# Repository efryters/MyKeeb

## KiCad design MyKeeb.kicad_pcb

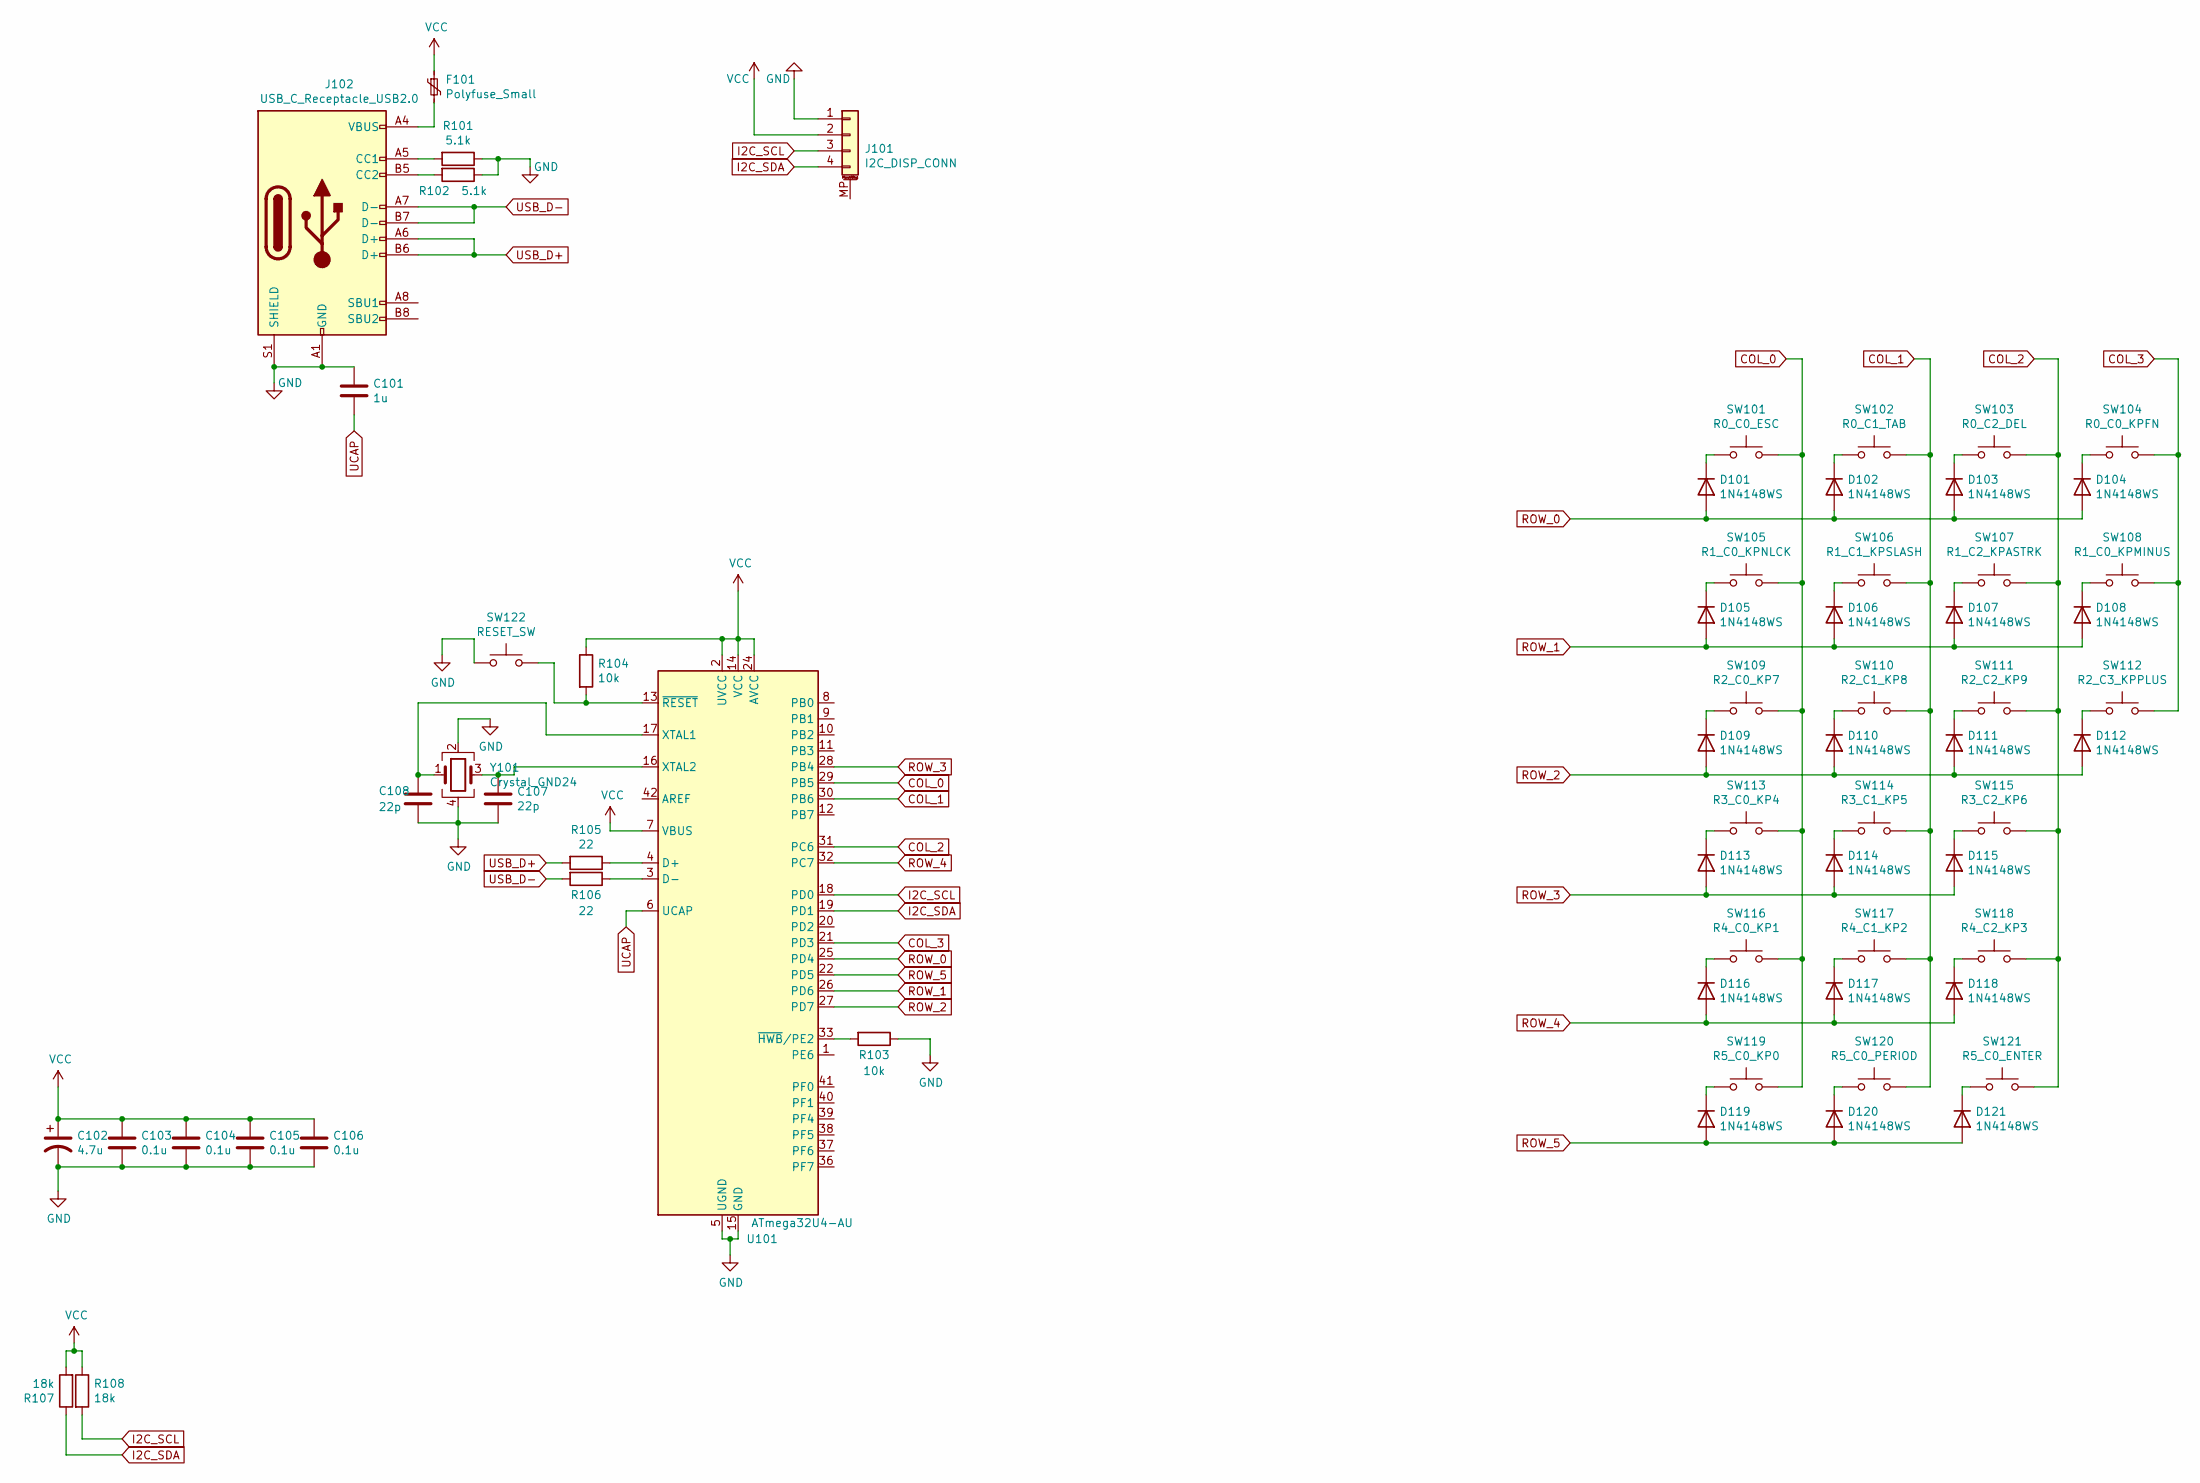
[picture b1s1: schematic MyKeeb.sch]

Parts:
C101: 1u; C_0603_1608Metric_Pad1.08x0.95mm_HandSolder
C102: 4.7u; C_Elec_4x5.4
C103, C104, C105, C106: 0.1u; C_0603_1608Metric_Pad1.08x0.95mm_HandSolder
C107, C108: 22p; C_0603_1608Metric_Pad1.08x0.95mm_HandSolder
D101, D102, D103, D104, D105, D106, D107, D108, D109, D110, D111, D112, D113, D114, D115, D116, D117, D118, D119, D120, D121: 1N4148WS; D_SOD-323
F101: Polyfuse_Small; Fuse_1206_3216Metric_Pad1.42x1.75mm_HandSolder
J101: I2C_DISP_CONN; PinSocket_1x04_P2.54mm_Horizontal
J102: USB_C_Receptacle_USB2.0; USB_C_Receptacle_GCT_USB4085
R101, R102: 5.1k; R_0603_1608Metric
R103, R104: 10k; R_0603_1608Metric
R105, R106: 22; R_0603_1608Metric
R107, R108: 18k; R_0603_1608Metric
SW101: R0_C0_ESC; SW_Cherry_MX_PCB_1.00u
SW102: R0_C1_TAB; SW_Cherry_MX_PCB_1.00u
SW103: R0_C2_DEL; SW_Cherry_MX_PCB_1.00u
SW104: R0_C0_KPFN; SW_Cherry_MX_PCB_1.00u
SW105: R1_C0_KPNLCK; SW_Cherry_MX_PCB_1.00u
SW106: R1_C1_KPSLASH; SW_Cherry_MX_PCB_1.00u
SW107: R1_C2_KPASTRK; SW_Cherry_MX_PCB_1.00u
SW108: R1_C0_KPMINUS; SW_Cherry_MX_PCB_1.00u
SW109: R2_C0_KP7; SW_Cherry_MX_PCB_1.00u
SW110: R2_C1_KP8; SW_Cherry_MX_PCB_1.00u
SW111: R2_C2_KP9; SW_Cherry_MX_PCB_1.00u
SW112: R2_C3_KPPLUS; SW_Cherry_MX_PCB_2.00u_Rotated
SW113: R3_C0_KP4; SW_Cherry_MX_PCB_1.00u
SW114: R3_C1_KP5; SW_Cherry_MX_PCB_1.00u
SW115: R3_C2_KP6; SW_Cherry_MX_PCB_1.00u
SW116: R4_C0_KP1; SW_Cherry_MX_PCB_1.00u
SW117: R4_C1_KP2; SW_Cherry_MX_PCB_1.00u
SW118: R4_C2_KP3; SW_Cherry_MX_PCB_1.00u
SW119: R5_C0_KP0; SW_Cherry_MX_PCB_2.00u
SW120: R5_C0_PERIOD; SW_Cherry_MX_PCB_1.00u
SW121: R5_C0_ENTER; SW_Cherry_MX_PCB_2.00u_Rotated
SW122: RESET_SW; SW_SPST_SKQG_WithoutStem
U101: ATmega32U4-AU; TQFP-44_10x10mm_P0.8mm
Y101: Crystal_GND24; Crystal_SMD_Abracon_ABM3B-4Pin_5.0x3.2mm

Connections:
COL_0: SW101.2, SW105.2, SW109.2, SW113.2, SW116.2, SW119.2, U101.29 (PB5)
COL_1: SW102.2, SW106.2, SW110.2, SW114.2, SW117.2, SW120.2, U101.30 (PB6)
COL_2: SW103.2, SW107.2, SW111.2, SW115.2, SW118.2, SW121.2, U101.31 (PC6)
COL_3: SW104.2, SW108.2, SW112.2, U101.21 (PD3)
GND: C101.1, C102.2, C103.2, C104.2, C105.2, C106.2, C107.2, C108.2, J101.1, J102.A1 (GND), J102.A12 (GND), J102.B1 (GND), J102.B12 (GND), J102.S1 (SHIELD), R101.1, R102.1, R103.1, SW122.1, U101.5 (UGND), U101.15 (GND), U101.23 (GND), U101.35 (GND), U101.43 (GND), Y101.2, Y101.4
I2C_SCL: J101.3, R108.2, U101.18 (PD0)
I2C_SDA: J101.4, R107.1, U101.19 (PD1)
unnamed: C107.1, U101.16 (XTAL2), Y101.3
unnamed: C108.1, U101.17 (XTAL1), Y101.1
unnamed: D101.1 (K), SW101.1
unnamed: D102.1 (K), SW102.1
unnamed: D103.1 (K), SW103.1
unnamed: D104.1 (K), SW104.1
unnamed: D105.1 (K), SW105.1
unnamed: D106.1 (K), SW106.1
unnamed: D107.1 (K), SW107.1
unnamed: D108.1 (K), SW108.1
unnamed: D109.1 (K), SW109.1
unnamed: D110.1 (K), SW110.1
unnamed: D111.1 (K), SW111.1
unnamed: D112.1 (K), SW112.1
unnamed: D113.1 (K), SW113.1
unnamed: D114.1 (K), SW114.1
unnamed: D115.1 (K), SW115.1
unnamed: D116.1 (K), SW116.1
unnamed: D117.1 (K), SW117.1
unnamed: D118.1 (K), SW118.1
unnamed: D119.1 (K), SW119.1
unnamed: D120.1 (K), SW120.1
unnamed: D121.1 (K), SW121.1
unnamed: F101.2, J102.A4 (VBUS), J102.A9 (VBUS), J102.B4 (VBUS), J102.B9 (VBUS)
unnamed: J102.A5 (CC1), R101.2
unnamed: J102.B5 (CC2), R102.2
unnamed: R103.2, U101.33 (~HWB~/PE2)
unnamed: R104.2, SW122.2, U101.13 (~RESET)
unnamed: R105.1, U101.4 (D+)
unnamed: R106.1, U101.3 (D-)
ROW_0: D101.2 (A), D102.2 (A), D103.2 (A), D104.2 (A), U101.25 (PD4)
ROW_1: D105.2 (A), D106.2 (A), D107.2 (A), D108.2 (A), U101.26 (PD6)
ROW_2: D109.2 (A), D110.2 (A), D111.2 (A), D112.2 (A), U101.27 (PD7)
ROW_3: D113.2 (A), D114.2 (A), D115.2 (A), U101.28 (PB4)
ROW_4: D116.2 (A), D117.2 (A), D118.2 (A), U101.32 (PC7)
ROW_5: D119.2 (A), D120.2 (A), D121.2 (A), U101.22 (PD5)
UCAP: C101.2, U101.6 (UCAP)
USB_D+: J102.A6 (D+), J102.B6 (D+), R105.2
USB_D-: J102.A7 (D-), J102.B7 (D-), R106.2
VCC: C102.1, C103.1, C104.1, C105.1, C106.1, F101.1, J101.2, R104.1, R107.2, R108.1, U101.2 (UVCC), U101.7 (VBUS), U101.14 (VCC), U101.24 (AVCC), U101.34 (VCC), U101.44 (AVCC)

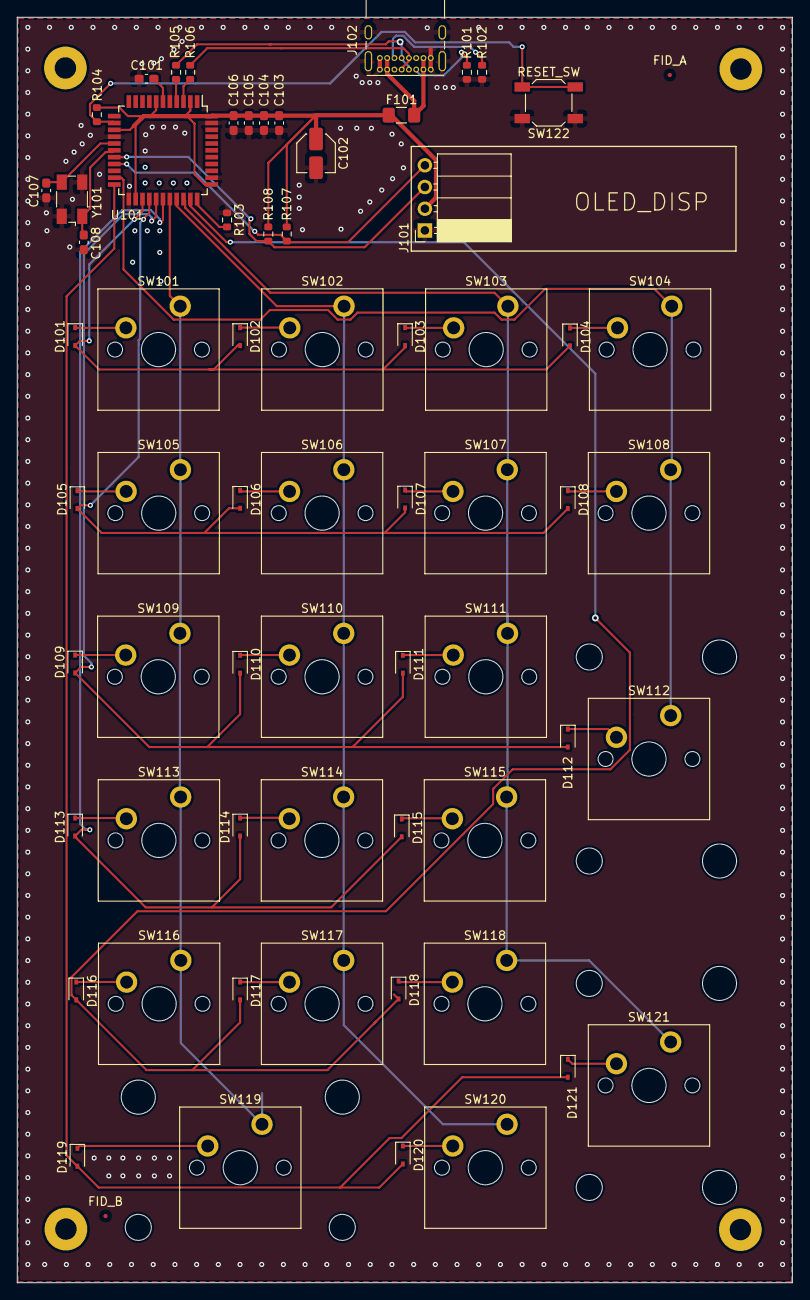
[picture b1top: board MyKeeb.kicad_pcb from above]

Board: 2 copper layers, 90.7 x 148.1 mm, 66 parts (0 on the bottom side), 47 nets.

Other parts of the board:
FID_A: Fiducial_0.5mm_Mask1.5mm
FID_B: Fiducial_0.5mm_Mask1.5mm

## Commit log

2021-03-29 Adding case 3d models
2021-03-31 Fix misplacement of KP_2-5
